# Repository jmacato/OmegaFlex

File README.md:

# OmegaFlex
A combined NAND/GPU signal/U10 relocation flexible PCB for Nintendo Wii revision 40/60

This flexible PCB combines the goodness of NAND, Wii's GPU signals and the U10 in one package. It also has breakouts for GameCube controller 1/2 data lines with pull up resistors, MODE pin pullup solder bridge pad and USB/Bluetooth data lines as well.

Its primary goal is to reduce the mess of magnet wires in portables and to make the Wii as something of a removable module that can be reused without resoldering when you want to upgrade your portables in the future.

PCBWay can fabricate this easily as well. Kinda expensive though and the ideal number of flex per batch is 25 pcs. But it's so worth it :)

## BitBuilt Thread
https://web.archive.org/web/20211211042716/https://bitbuilt.net/forums/index.php?threads/omegaflex-combined-nand-gpu-signal-u10-relocation-flex-pcb.4679/

## Licensing

This project is covered under the terms of CERN Open Hardware Licence Version 2 - Strongly Reciprocal. This license mandates that any modifications or re-derivations of this project shall be attributed back under the same license and published as well.

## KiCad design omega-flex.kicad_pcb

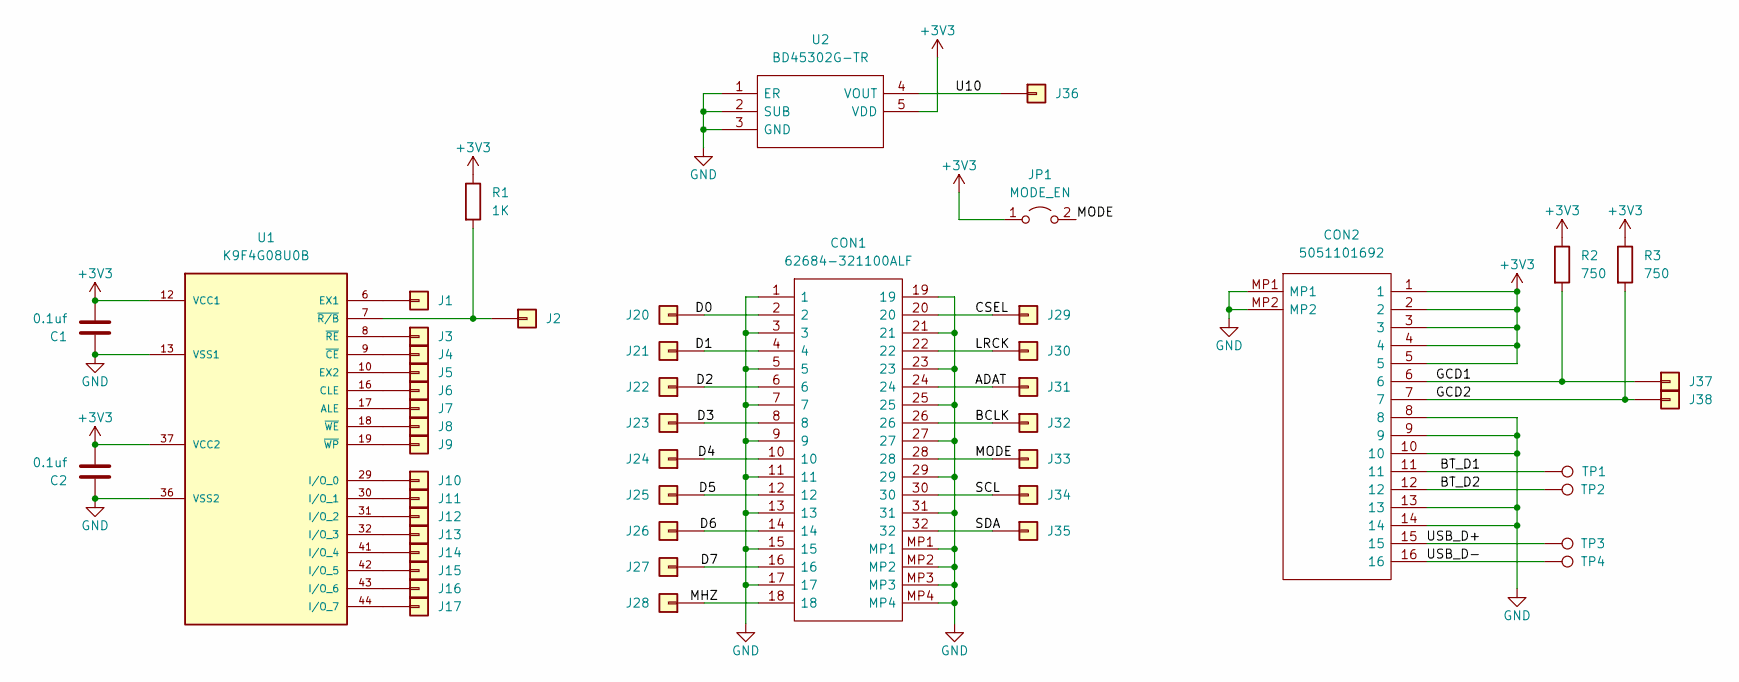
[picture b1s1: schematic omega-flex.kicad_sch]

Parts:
C1, C2: 0.1uf; C_0402_1005Metric_Pad0.74x0.62mm_HandSolder
CON1: 62684-321100ALF; 62684321100ALF; Manufacturer_Part_Number 62684-321100ALF; Mouser Part Number 649-62684-321100ALF
CON2: 5051101692; Manufacturer_Part_Number 5051101692
J1, J2, J3, J4, J5, J6, J7, J8, J9, J10, J11, J12, J13, J14, J15, J16, J17, J20, J21, J22, J23, J24, J25, J26, J27, J28, J29, J30, J31, J32, J33, J34, J35, J36, J37, J38: Conn_01x01; wii-single-via-0.45mm
JP1: MODE_EN; SolderJumper-2_P1.3mm_Open_Pad1.0x1.5mm
R1: 1K; R_0402_1005Metric_Pad0.72x0.64mm_HandSolder
R2, R3: 750; R_0402_1005Metric_Pad0.72x0.64mm_HandSolder
TP1, TP2, TP3, TP4: TestPoint; TestPoint_Pad_D1.5mm
U1: K9F4G08U0B; Wii-TSOP48-trimmed; MPN S34ML02G100TFI000
U2: BD45302G-TR; SOT95P280X125-5N; Manufacturer_Part_Number BD45302G-TR; Mouser Part Number 755-BD45302G-TR

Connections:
+3V3: C1.2, C2.2, CON2.1, CON2.2, CON2.3, CON2.4, CON2.5, JP1.1 (A), R1.1, R2.1, R3.1, U1.12 (VCC1), U1.37 (VCC2), U2.5 (VDD)
/ADAT: CON1.24, J31.1
/BCLK: CON1.26, J32.1
/BT_D1: CON2.11, TP1.1
/BT_D2: CON2.12, TP2.1
/CSEL: CON1.20, J29.1
/D0: CON1.2, J20.1
/D1: CON1.4, J21.1
/D2: CON1.6, J22.1
/D3: CON1.8, J23.1
/D4: CON1.10, J24.1
/D5: CON1.12, J25.1
/D6: CON1.14, J26.1
/D7: CON1.16, J27.1
/GCD1: CON2.6, J37.1, R2.2
/GCD2: CON2.7, J38.1, R3.2
/LRCK: CON1.22, J30.1
/MHZ: CON1.18, J28.1
/MODE: CON1.28, J33.1, JP1.2 (B)
/SCL: CON1.30, J34.1
/SDA: CON1.32, J35.1
/U10: J36.1, U2.4 (VOUT)
/USB_D+: CON2.15, TP3.1
/USB_D-: CON2.16, TP4.1
GND: C1.1, C2.1, CON1.1, CON1.3, CON1.5, CON1.7, CON1.9, CON1.11, CON1.13, CON1.15, CON1.17, CON1.19, CON1.21, CON1.23, CON1.25, CON1.27, CON1.29, CON1.31, CON1.MP1, CON1.MP2, CON1.MP3, CON1.MP4, CON2.8, CON2.9, CON2.10, CON2.13, CON2.14, CON2.MP1, CON2.MP2, U1.13 (VSS1), U1.36 (VSS2), U2.1 (ER), U2.2 (SUB), U2.3 (GND)
unnamed: J1.1, U1.6 (EX1)
unnamed: J2.1, R1.2, U1.7 (~R/B)
unnamed: J3.1, U1.8 (~RE)
unnamed: J4.1, U1.9 (~CE)
unnamed: J5.1, U1.10 (EX2)
unnamed: J6.1, U1.16 (CLE)
unnamed: J7.1, U1.17 (ALE)
unnamed: J8.1, U1.18 (~WE)
unnamed: J9.1, U1.19 (~WP)
unnamed: J10.1, U1.29 (I/O_0)
unnamed: J11.1, U1.30 (I/O_1)
unnamed: J12.1, U1.31 (I/O_2)
unnamed: J13.1, U1.32 (I/O_3)
unnamed: J14.1, U1.41 (I/O_4)
unnamed: J15.1, U1.42 (I/O_5)
unnamed: J16.1, U1.43 (I/O_6)
unnamed: J17.1, U1.44 (I/O_7)

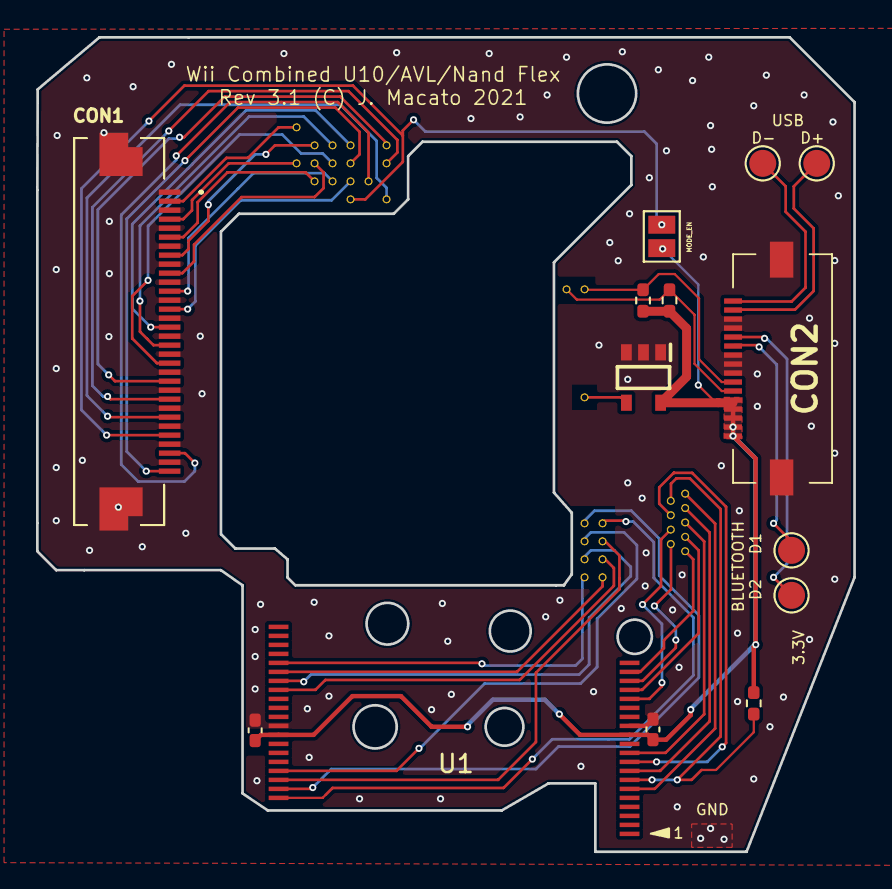
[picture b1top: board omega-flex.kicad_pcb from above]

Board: 2 copper layers, 45.4 x 45.2 mm, 50 parts (0 on the bottom side), 42 nets.
